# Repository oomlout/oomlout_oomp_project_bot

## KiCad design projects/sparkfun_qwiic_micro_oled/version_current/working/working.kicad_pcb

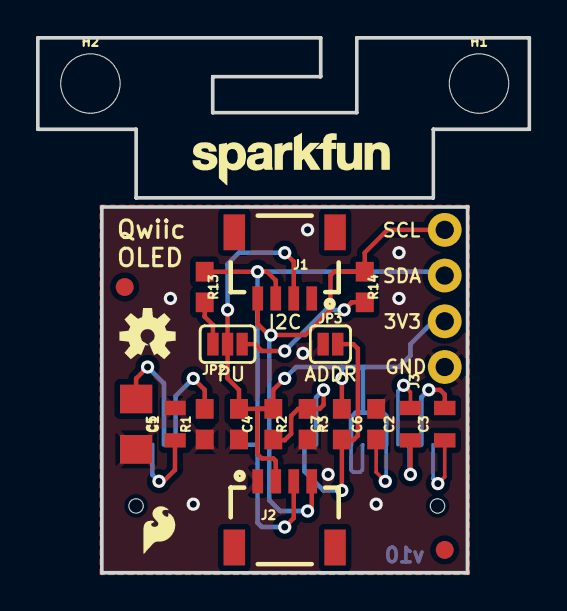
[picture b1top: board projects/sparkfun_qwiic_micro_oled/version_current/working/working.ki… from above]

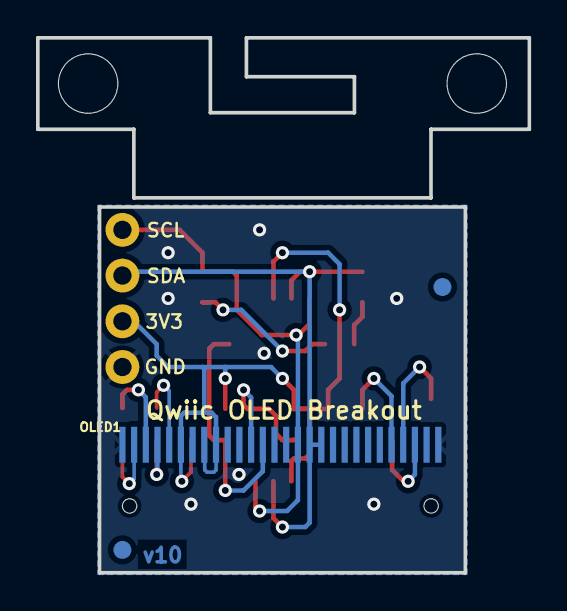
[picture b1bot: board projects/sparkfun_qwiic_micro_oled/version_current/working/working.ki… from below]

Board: 2 copper layers, 27.3 x 29.7 mm, 29 parts (3 on the bottom side), 15 nets.

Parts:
C1: 2.2uF; 0805
C2, C3: 1.0uF; 0805
C4, C6, C7: 1.0uF; 0603
C5: 4.7uF; 1206
FID1, FID2, FID3, FID4: FIDUCIAL1X2; FIDUCIAL-1X2
FRAME1: FRAME-LETTER; CREATIVE_COMMONS
H1, H2: STAND-OFF
J1, J2: 1X04_1MM_RA
J3: 1X04_NO_SILK
JP2: SMT-JUMPER_3_2-NC_PASTE_SILK
JP3: SMT-JUMPER_2_NO_SILK
LOGO1: REVISION
LOGO2: SFE_LOGO_FLAME.1_INCH; SFE_LOGO_FLAME_.1
LOGO3: OSHW-LOGOS; OSHW-LOGO-S
LOGO4: SFE_LOGO_NAME.1_INCH; SFE_LOGO_NAME_.1
OLED1: OLED0.66; OLED-0.66-64X48
R1: 390k; 0603
R2, R3: 10k; 0603
R13, R14: 4.7k; 0603

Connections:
C1P: C2.1, OLED1.4
C2N: C3.2, OLED1.3
D0/SCK: J1.4, J2.4, J3.4, OLED1.16, R14.1
D1/MOSI: J1.3, J2.3, J3.3, OLED1.17, OLED1.18, R13.1
D/C: JP3.2, OLED1.13, R3.1
GND: C1.2, C4.2, C5.2, C6.2, C7.2, J1.1, J2.1, J3.1, JP3.1, OLED1.1, OLED1.7, OLED1.10, OLED1.27, OLED1.28, R1.1
IREF: OLED1.24, R1.2
unnamed: C3.1, OLED1.2
unnamed: C2.2, OLED1.5
unnamed: JP2.3, R13.2
unnamed: JP2.1, R14.2
RESET: C7.1, OLED1.12, R2.2
VCC: C1.1, OLED1.26
VCOMH: C5.1, OLED1.25
VDD: C4.1, C6.1, J1.2, J2.2, J3.2, JP2.2, OLED1.6, OLED1.8, OLED1.9, R2.1, R3.2

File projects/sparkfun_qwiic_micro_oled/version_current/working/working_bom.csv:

"Id";"Designator";"Footprint";"Quantity";"Designation";"Supplier and ref";
1;"C1";"0805";1;"2.2uF";;;
2;"JP3";"SMT-JUMPER_2_NO_SILK";1;"";;;
3;"C6,C7,C4";"0603";3;"1.0uF";;;
4;"R2,R3";"0603";2;"10k";;;
5;"LOGO1";"REVISION";1;"REVISION";;;
6;"R1";"0603";1;"390k";;;
7;"J2,J1";"1X04_1MM_RA";2;"";;;
8;"H1,H2";"STAND-OFF";2;"STAND-OFF";;;
9;"FRAME1";"CREATIVE_COMMONS";1;"FRAME-LETTER";;;
10;"C3,C2";"0805";2;"1.0uF";;;
11;"C5";"1206";1;"4.7uF";;;
12;"LOGO4";"SFE_LOGO_NAME_.1";1;"SFE_LOGO_NAME.1_INCH";;;
13;"JP2";"SMT-JUMPER_3_2-NC_PASTE_SILK";1;"";;;
14;"J3";"1X04_NO_SILK";1;"";;;
15;"LOGO2";"SFE_LOGO_FLAME_.1";1;"SFE_LOGO_FLAME.1_INCH";;;
16;"FID2,FID1,FID4,FID3";"FIDUCIAL-1X2";4;"FIDUCIAL1X2";;;
17;"R14,R13";"0603";2;"4.7k";;;
18;"LOGO3";"OSHW-LOGO-S";1;"OSHW-LOGOS";;;
19;"OLED1";"OLED-0.66-64X48";1;"OLED0.66";;;

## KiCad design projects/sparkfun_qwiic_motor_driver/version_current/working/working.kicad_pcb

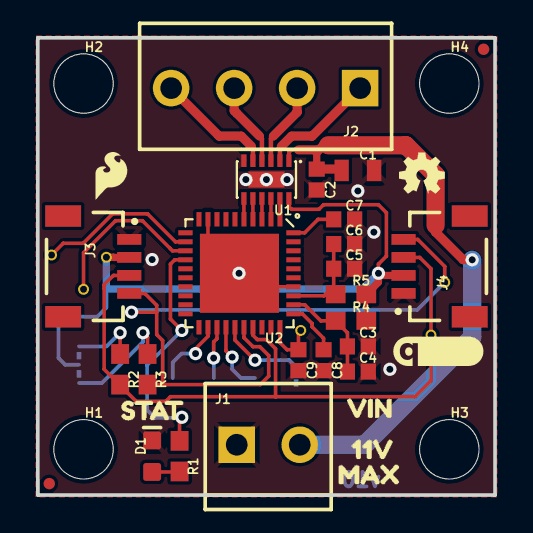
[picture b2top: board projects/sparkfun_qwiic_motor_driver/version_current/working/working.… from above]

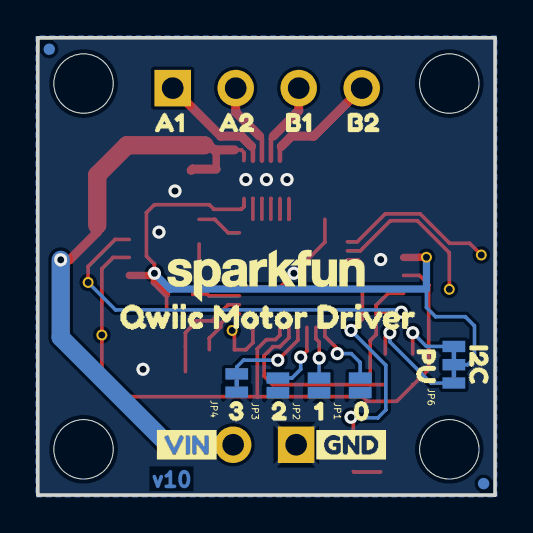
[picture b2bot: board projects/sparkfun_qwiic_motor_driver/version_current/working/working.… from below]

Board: 2 copper layers, 25.4 x 25.4 mm, 62 parts (21 on the bottom side), 29 nets.

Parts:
C1: 10uF; 0805
C2, C4, C6, C9: 0.1uF; 0402
C3, C5, C7, C8: 1.0uF; 0402
D1: BLUE; LED-0603
FD1, FD2, FD3, FD4: FIDUCIALUFIDUCIAL; FIDUCIAL-MICRO
FRAME1: FRAME-LETTER; CREATIVE_COMMONS
H1, H2, H3, H4: STAND-OFF
J1: Power In; SCREWTERMINAL-3.5MM-2
J2: Motor Connections; SCREWTERMINAL-3.5MM-4
J3, J4: Qwiic; JST04_1MM_RA
JP1, JP2, JP3: JUMPER-PAD-2; SMT-JUMPER_2_NO_NO-SILK
JP4: JUMPER-PAD-2; SMT-JUMPER_2_NC_TRACE_NO-SILK
JP6: JUMPER-SMT_3_2-NC_TRACE_NO-SILK; SMT-JUMPER_3_2-NC_TRACE_NO-SILK
LOGO2: OSHW-LOGOMINI; OSHW-LOGO-MINI
LOGO3: SFE_LOGO_NAME.1_INCH; SFE_LOGO_NAME_.1
R1: 470; 0603
R2, R3: 4.7k; 0603
R4, R5: 1; 0603
TP1, TP2, TP3, TP4, TP5, TP6: TP_15TH
U1: DRV8835; WSON-12
U2: CY8C4245LQI-483; QFN-40
U$1: QWIIC_LOGO_5MM; QWIIC_5MM
U$2: STAT4
U$3: GND3
U$4: VIN2
U$5: 05
U$6: 16
U$7: 27
U$8: 38
U$9: A110
U$10: A211
U$11: B112
U$12: B213
U$13: 11V7
U$14: MAX8
U$15: VIN6
U$16: I2C0
U$17: PU1
U$18: QWIIC_MOTOR_DRIVER0
U$19: SFE_LOGO_FLAME_.1

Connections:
3.3V: J3.2, J4.2, JP6.2, R4.2, R5.2, TP1.P$1, U1.12
AOUT1: J2.1, U1.2
AOUT2: J2.2, U1.3
BOUT1: J2.3, U1.4
BOUT2: J2.4, U1.5
GND: C1.2, C2.2, C3.2, C4.2, C5.2, C6.2, C7.2, C8.2, C9.2, D1.C, J1.1, J3.1, J4.1, JP1.1, JP2.1, JP3.1, JP4.1, U1.6, U1.PAD, U2.9, U2.34, U2.EP
MODEB0: JP1.2, U2.22
MODEB1: JP2.2, U2.23
MODEB2: JP3.2, U2.24
MODEB3: JP4.2, U2.25
unnamed: C8.1, U2.31
unnamed: C5.1, C6.1, R5.1, U2.33
unnamed: C7.1, U2.40
unnamed: D1.A, R1.2
unnamed: JP6.1, R3.1
unnamed: JP6.3, R2.1
P2.0: U1.11, U2.1
P2.1: U1.10, U2.2
P2.2: U1.9, U2.3
P2.3: U1.8, U2.4
P2.4: U1.7, U2.5
P3.2: TP2.P$1, U2.12
P3.3: TP3.P$1, U2.13
SCL: J3.4, J4.4, R3.2, TP6.P$1, U2.26
SDA: J3.3, J4.3, R2.2, TP5.P$1, U2.27
SLED: R1.1, U2.14
VDDD: C3.1, C4.1, R4.1, U2.32
VIN: C1.1, C2.1, J1.2, U1.1
~RESET: C9.1, TP4.P$1, U2.30

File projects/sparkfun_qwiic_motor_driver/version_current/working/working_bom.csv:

"Id";"Designator";"Footprint";"Quantity";"Designation";"Supplier and ref";
1;"H4,H3,H1,H2";"STAND-OFF";4;"STAND-OFF";;;
2;"TP5,TP2,TP3,TP4,TP1,TP6";"TP_15TH";6;"";;;
3;"C5,C7,C3,C8";"0402";4;"1.0uF";;;
4;"C9,C6,C2,C4";"0402";4;"0.1uF";;;
5;"U$1";"QWIIC_5MM";1;"QWIIC_LOGO_5MM";;;
6;"FD1,FD3,FD2,FD4";"FIDUCIAL-MICRO";4;"FIDUCIALUFIDUCIAL";;;
7;"U1";"WSON-12";1;"DRV8835";;;
8;"C1";"0805";1;"10uF";;;
9;"J4,J3";"JST04_1MM_RA";2;"Qwiic";;;
10;"U2";"QFN-40";1;"CY8C4245LQI-483";;;
11;"FRAME1";"CREATIVE_COMMONS";1;"FRAME-LETTER";;;
12;"U$14";"MAX8";1;"";;;
13;"R2,R3";"0603";2;"4.7k";;;
14;"U$13";"11V7";1;"";;;
15;"LOGO2";"OSHW-LOGO-MINI";1;"OSHW-LOGOMINI";;;
16;"R1";"0603";1;"470";;;
17;"J2";"SCREWTERMINAL-3.5MM-4";1;"Motor Connections";;;
18;"R4,R5";"0603";2;"1";;;
19;"U$15";"VIN6";1;"";;;
20;"U$2";"STAT4";1;"";;;
21;"U$19";"SFE_LOGO_FLAME_.1";1;"";;;
22;"D1";"LED-0603";1;"BLUE";;;
23;"J1";"SCREWTERMINAL-3.5MM-2";1;"Power In";;;
24;"U$16";"I2C0";1;"";;;
25;"JP3,JP1,JP2";"SMT-JUMPER_2_NO_NO-SILK";3;"JUMPER-PAD-2";;;
26;"JP4";"SMT-JUMPER_2_NC_TRACE_NO-SILK";1;"JUMPER-PAD-2";;;
27;"LOGO3";"SFE_LOGO_NAME_.1";1;"SFE_LOGO_NAME.1_INCH";;;
28;"U$8";"38";1;"";;;
29;"U$11";"B112";1;"";;;
30;"U$18";"QWIIC_MOTOR_DRIVER0";1;"";;;
31;"U$4";"VIN2";1;"";;;
32;"U$7";"27";1;"";;;
33;"U$5";"05";1;"";;;
34;"U$10";"A211";1;"";;;
35;"U$17";"PU1";1;"";;;
36;"U$6";"16";1;"";;;
37;"U$12";"B213";1;"";;;
38;"U$9";"A110";1;"";;;
39;"JP6";"SMT-JUMPER_3_2-NC_TRACE_NO-SILK";1;"JUMPER-SMT_3_2-NC_TRACE_NO-SILK";;;
40;"U$3";"GND3";1;"";;;

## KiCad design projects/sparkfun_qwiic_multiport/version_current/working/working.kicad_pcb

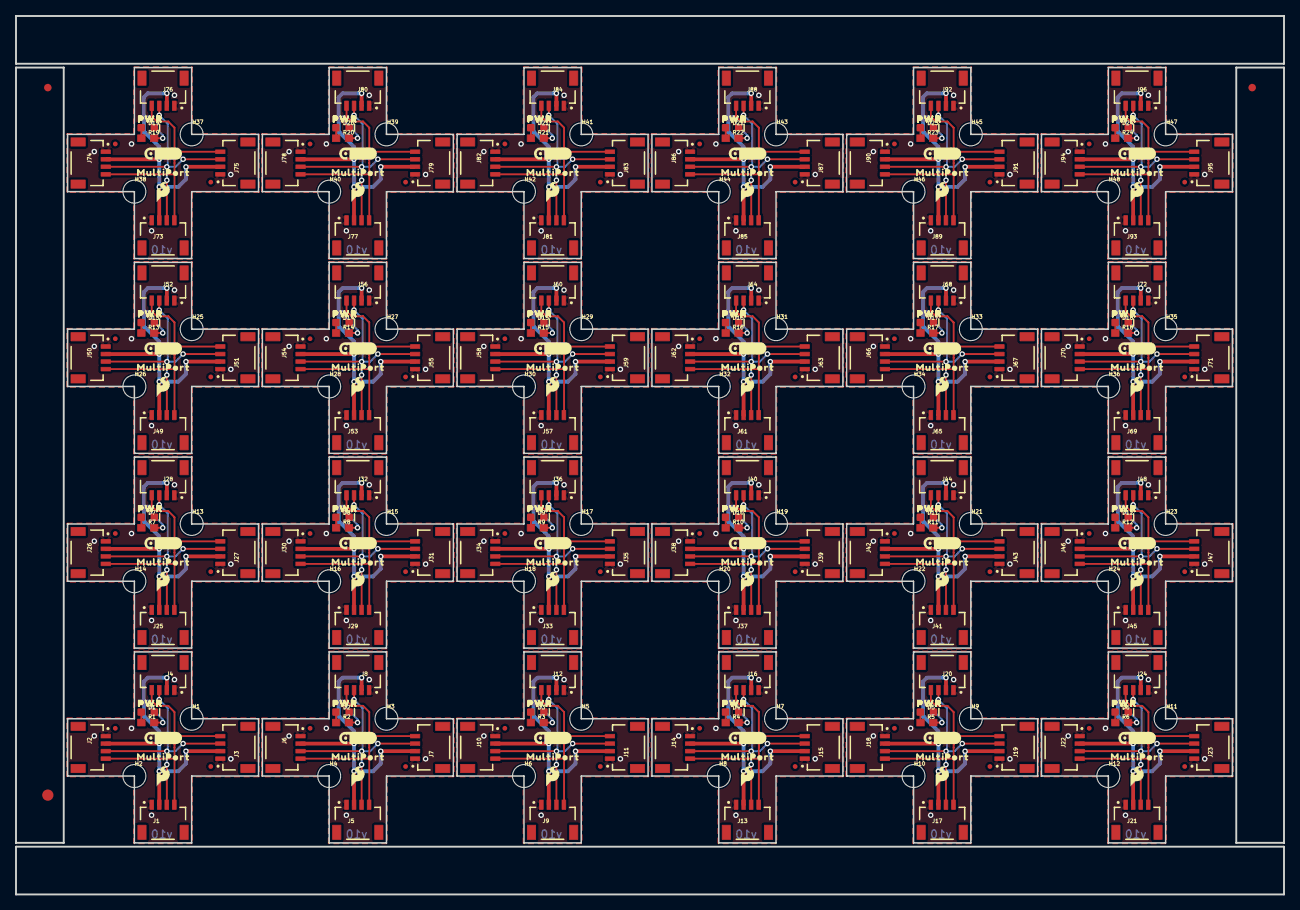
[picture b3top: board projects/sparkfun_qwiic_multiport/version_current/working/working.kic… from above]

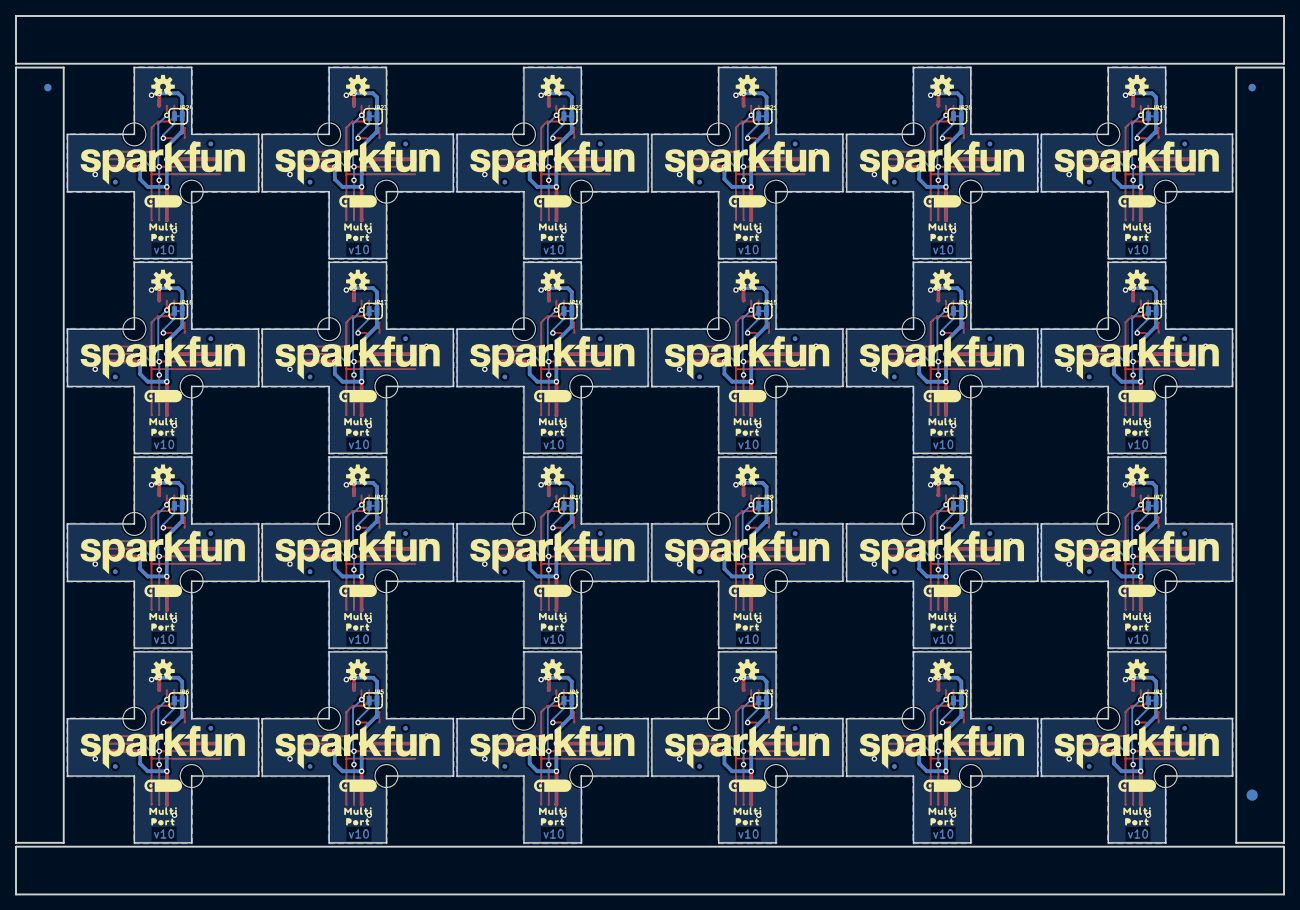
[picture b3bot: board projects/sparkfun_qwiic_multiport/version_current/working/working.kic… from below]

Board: 2 copper layers, 168.7 x 116.8 mm, 582 parts (219 on the bottom side), 144 nets.

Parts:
D1, D2, D3, D4, D5, D6, D7, D8, D9, D10, D11, D12, D13, D14, D15, D16, D17, D18, D19, D20, D21, D22, D23, D24: RED; LED-0603
E$1, E$2, E$3, E$4: FIDUCIAL-1X2
E$5, E$6: FIDUCIAL-1.5X3
FD1, FD2, FD3, FD4, FD5, FD6, FD7, FD8, FD9, FD10, FD11, FD12, FD13, FD14, FD15, FD16, FD17, FD18, FD19, FD20, FD21, FD22, FD23, FD24, FD25, FD26, FD27, FD28, FD29, FD30, FD31, FD32, FD33, FD34, FD35, FD36, FD37, FD38, FD39, FD40, FD41, FD42, FD43, FD44, FD45, FD46, FD47, FD48, FD49, FD50, FD51, FD52, FD53, FD54, FD55, FD56, FD57, FD58, FD59, FD60, FD61, FD62, FD63, FD64, FD65, FD66, FD67, FD68, FD69, FD70, FD71, FD72, FD73, FD74, FD75, FD76, FD77, FD78, FD79, FD80, FD81, FD82, FD83, FD84, FD85, FD86, FD87, FD88, FD89, FD90, FD91, FD92, FD93, FD94, FD95, FD96: FIDUCIALUFIDUCIAL; FIDUCIAL-MICRO
H1, H2, H3, H4, H5, H6, H7, H8, H9, H10, H11, H12, H13, H14, H15, H16, H17, H18, H19, H20, H21, H22, H23, H24, H25, H26, H27, H28, H29, H30, H31, H32, H33, H34, H35, H36, H37, H38, H39, H40, H41, H42, H43, H44, H45, H46, H47, H48: STAND-OFFTIGHT; STAND-OFF-TIGHT
J1, J2, J3, J4, J5, J6, J7, J8, J9, J10, J11, J12, J13, J14, J15, J16, J17, J18, J19, J20, J21, J22, J23, J24, J25, J26, J27, J28, J29, J30, J31, J32, J33, J34, J35, J36, J37, J38, J39, J40, J41, J42, J43, J44, J45, J46, J47, J48, J49, J50, J51, J52, J53, J54, J55, J56, J57, J58, J59, J60, J61, J62, J63, J64, J65, J66, J67, J68, J69, J70, J71, J72, J73, J74, J75, J76, J77, J78, J79, J80, J81, J82, J83, J84, J85, J86, J87, J88, J89, J90, J91, J92, J93, J94, J95, J96: QWIIC_RIGHT_ANGLE; JST04_1MM_RA
JP1, JP2, JP3, JP4, JP5, JP6, JP7, JP8, JP9, JP10, JP11, JP12, JP13, JP14, JP15, JP16, JP17, JP18, JP19, JP20, JP21, JP22, JP23, JP24: PWR_LED; SMT-JUMPER_2_NC_TRACE_SILK
LOGO1, LOGO2, LOGO5, LOGO6, LOGO9, LOGO10, LOGO13, LOGO14, LOGO17, LOGO18, LOGO21, LOGO22, LOGO25, LOGO26, LOGO29, LOGO30, LOGO33, LOGO34, LOGO37, LOGO38, LOGO41, LOGO42, LOGO45, LOGO46, LOGO49, LOGO50, LOGO53, LOGO54, LOGO57, LOGO58, LOGO61, LOGO62, LOGO65, LOGO66, LOGO69, LOGO70, LOGO73, LOGO74, LOGO77, LOGO78, LOGO81, LOGO82, LOGO85, LOGO86, LOGO89, LOGO90, LOGO93, LOGO94: QWIIC_LOGO_5MM; QWIIC_5MM
LOGO3, LOGO7, LOGO11, LOGO15, LOGO19, LOGO23, LOGO27, LOGO31, LOGO35, LOGO39, LOGO43, LOGO47, LOGO51, LOGO55, LOGO59, LOGO63, LOGO67, LOGO71, LOGO75, LOGO79, LOGO83, LOGO87, LOGO91, LOGO95: OSHW-LOGOS; OSHW-LOGO-S
LOGO4, LOGO8, LOGO12, LOGO16, LOGO20, LOGO24, LOGO28, LOGO32, LOGO36, LOGO40, LOGO44, LOGO48, LOGO52, LOGO56, LOGO60, LOGO64, LOGO68, LOGO72, LOGO76, LOGO80, LOGO84, LOGO88, LOGO92, LOGO96: SFE_LOGO_NAME.2_INCH; SFE_LOGO_NAME_.2
R1, R2, R3, R4, R5, R6, R7, R8, R9, R10, R11, R12, R13, R14, R15, R16, R17, R18, R19, R20, R21, R22, R23, R24: 1k; 0603
U$1, U$6, U$9, U$10, U$16, U$19, U$23, U$26, U$30, U$33, U$37, U$40, U$44, U$47, U$51, U$54, U$58, U$61, U$65, U$68, U$72, U$75, U$79, U$82, U$86, U$89, U$93, U$96, U$100, U$103, U$107, U$110, U$114, U$117, U$121, U$124, U$128, U$131, U$135, U$138, U$142, U$145, U$149, U$152, U$156, U$159, U$163, U$166: PWR0
U$2, U$3, U$15, U$22, U$29, U$36, U$43, U$50, U$57, U$64, U$71, U$78, U$85, U$92, U$99, U$106, U$113, U$120, U$127, U$134, U$141, U$148, U$155, U$162: SFE_LOGO_FLAME_.1
U$4, U$12, U$20, U$27, U$34, U$41, U$48, U$55, U$62, U$69, U$76, U$83, U$90, U$97, U$104, U$111, U$118, U$125, U$132, U$139, U$146, U$153, U$160, U$167: MULTIPORT0
U$5, U$14, U$21, U$28, U$35, U$42, U$49, U$56, U$63, U$70, U$77, U$84, U$91, U$98, U$105, U$112, U$119, U$126, U$133, U$140, U$147, U$154, U$161, U$168: #PWR#0
U$7, U$11, U$17, U$24, U$31, U$38, U$45, U$52, U$59, U$66, U$73, U$80, U$87, U$94, U$101, U$108, U$115, U$122, U$129, U$136, U$143, U$150, U$157, U$164: MULTI0
U$8, U$13, U$18, U$25, U$32, U$39, U$46, U$53, U$60, U$67, U$74, U$81, U$88, U$95, U$102, U$109, U$116, U$123, U$130, U$137, U$144, U$151, U$158, U$165: PORT0

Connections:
3.3V: J1.2, J2.2, J3.2, J4.2, JP1.2
3.3V1: J5.2, J6.2, J7.2, J8.2, JP2.2
3.3V2: J9.2, J10.2, J11.2, J12.2, JP3.2
3.3V3: J13.2, J14.2, J15.2, J16.2, JP4.2
3.3V4: J17.2, J18.2, J19.2, J20.2, JP5.2
3.3V5: J21.2, J22.2, J23.2, J24.2, JP6.2
3.3V6: J25.2, J26.2, J27.2, J28.2, JP7.2
3.3V7: J29.2, J30.2, J31.2, J32.2, JP8.2
3.3V8: J33.2, J34.2, J35.2, J36.2, JP9.2
3.3V9: J37.2, J38.2, J39.2, J40.2, JP10.2
3.3V10: J41.2, J42.2, J43.2, J44.2, JP11.2
3.3V11: J45.2, J46.2, J47.2, J48.2, JP12.2
3.3V12: J49.2, J50.2, J51.2, J52.2, JP13.2
3.3V13: J53.2, J54.2, J55.2, J56.2, JP14.2
3.3V14: J57.2, J58.2, J59.2, J60.2, JP15.2
3.3V15: J61.2, J62.2, J63.2, J64.2, JP16.2
3.3V16: J65.2, J66.2, J67.2, J68.2, JP17.2
3.3V17: J69.2, J70.2, J71.2, J72.2, JP18.2
3.3V18: J73.2, J74.2, J75.2, J76.2, JP19.2
3.3V19: J77.2, J78.2, J79.2, J80.2, JP20.2
3.3V20: J81.2, J82.2, J83.2, J84.2, JP21.2
3.3V21: J85.2, J86.2, J87.2, J88.2, JP22.2
3.3V22: J89.2, J90.2, J91.2, J92.2, JP23.2
3.3V23: J93.2, J94.2, J95.2, J96.2, JP24.2
GND: D1.C, J1.1, J2.1, J3.1, J4.1
GND1: D2.C, J5.1, J6.1, J7.1, J8.1
GND2: D3.C, J9.1, J10.1, J11.1, J12.1
GND3: D4.C, J13.1, J14.1, J15.1, J16.1
GND4: D5.C, J17.1, J18.1, J19.1, J20.1
GND5: D6.C, J21.1, J22.1, J23.1, J24.1
GND6: D7.C, J25.1, J26.1, J27.1, J28.1
GND7: D8.C, J29.1, J30.1, J31.1, J32.1
GND8: D9.C, J33.1, J34.1, J35.1, J36.1
GND9: D10.C, J37.1, J38.1, J39.1, J40.1
GND10: D11.C, J41.1, J42.1, J43.1, J44.1
GND11: D12.C, J45.1, J46.1, J47.1, J48.1
GND12: D13.C, J49.1, J50.1, J51.1, J52.1
GND13: D14.C, J53.1, J54.1, J55.1, J56.1
GND14: D15.C, J57.1, J58.1, J59.1, J60.1
GND15: D16.C, J61.1, J62.1, J63.1, J64.1
GND16: D17.C, J65.1, J66.1, J67.1, J68.1
GND17: D18.C, J69.1, J70.1, J71.1, J72.1
GND18: D19.C, J73.1, J74.1, J75.1, J76.1
GND19: D20.C, J77.1, J78.1, J79.1, J80.1
GND20: D21.C, J81.1, J82.1, J83.1, J84.1
GND21: D22.C, J85.1, J86.1, J87.1, J88.1
GND22: D23.C, J89.1, J90.1, J91.1, J92.1
GND23: D24.C, J93.1, J94.1, J95.1, J96.1
unnamed: D1.A, R1.1
unnamed: JP1.1, R1.2
unnamed: D2.A, R2.1
unnamed: JP2.1, R2.2
unnamed: D3.A, R3.1
unnamed: JP3.1, R3.2
unnamed: D4.A, R4.1
unnamed: JP4.1, R4.2
unnamed: D5.A, R5.1
unnamed: JP5.1, R5.2
unnamed: D6.A, R6.1
unnamed: JP6.1, R6.2
unnamed: D7.A, R7.1
unnamed: JP7.1, R7.2
unnamed: D8.A, R8.1
unnamed: JP8.1, R8.2
unnamed: D9.A, R9.1
unnamed: JP9.1, R9.2
unnamed: D10.A, R10.1
unnamed: JP10.1, R10.2
unnamed: D11.A, R11.1
unnamed: JP11.1, R11.2
unnamed: D12.A, R12.1
unnamed: JP12.1, R12.2
unnamed: D13.A, R13.1
unnamed: JP13.1, R13.2
unnamed: D14.A, R14.1
unnamed: JP14.1, R14.2
unnamed: D15.A, R15.1
unnamed: JP15.1, R15.2
unnamed: D16.A, R16.1
unnamed: JP16.1, R16.2
unnamed: D17.A, R17.1
unnamed: JP17.1, R17.2
unnamed: D18.A, R18.1
unnamed: JP18.1, R18.2
unnamed: D19.A, R19.1
unnamed: JP19.1, R19.2
unnamed: D20.A, R20.1
unnamed: JP20.1, R20.2
unnamed: D21.A, R21.1
unnamed: JP21.1, R21.2
unnamed: D22.A, R22.1
unnamed: JP22.1, R22.2
unnamed: D23.A, R23.1
unnamed: JP23.1, R23.2
unnamed: D24.A, R24.1
unnamed: JP24.1, R24.2
SCL: J1.4, J2.4, J3.4, J4.4
SCL1: J5.4, J6.4, J7.4, J8.4
SCL2: J9.4, J10.4, J11.4, J12.4
SCL3: J13.4, J14.4, J15.4, J16.4
SCL4: J17.4, J18.4, J19.4, J20.4
SCL5: J21.4, J22.4, J23.4, J24.4
SCL6: J25.4, J26.4, J27.4, J28.4
SCL7: J29.4, J30.4, J31.4, J32.4
SCL8: J33.4, J34.4, J35.4, J36.4
SCL9: J37.4, J38.4, J39.4, J40.4
SCL10: J41.4, J42.4, J43.4, J44.4
SCL11: J45.4, J46.4, J47.4, J48.4
SCL12: J49.4, J50.4, J51.4, J52.4
SCL13: J53.4, J54.4, J55.4, J56.4
SCL14: J57.4, J58.4, J59.4, J60.4
SCL15: J61.4, J62.4, J63.4, J64.4
SCL16: J65.4, J66.4, J67.4, J68.4
SCL17: J69.4, J70.4, J71.4, J72.4
SCL18: J73.4, J74.4, J75.4, J76.4
SCL19: J77.4, J78.4, J79.4, J80.4
SCL20: J81.4, J82.4, J83.4, J84.4
SCL21: J85.4, J86.4, J87.4, J88.4
SCL22: J89.4, J90.4, J91.4, J92.4
SCL23: J93.4, J94.4, J95.4, J96.4
SDA: J1.3, J2.3, J3.3, J4.3
SDA1: J5.3, J6.3, J7.3, J8.3
SDA2: J9.3, J10.3, J11.3, J12.3
SDA3: J13.3, J14.3, J15.3, J16.3
SDA4: J17.3, J18.3, J19.3, J20.3
SDA5: J21.3, J22.3, J23.3, J24.3
SDA6: J25.3, J26.3, J27.3, J28.3
SDA7: J29.3, J30.3, J31.3, J32.3
SDA8: J33.3, J34.3, J35.3, J36.3
SDA9: J37.3, J38.3, J39.3, J40.3
SDA10: J41.3, J42.3, J43.3, J44.3
SDA11: J45.3, J46.3, J47.3, J48.3
SDA12: J49.3, J50.3, J51.3, J52.3
SDA13: J53.3, J54.3, J55.3, J56.3
SDA14: J57.3, J58.3, J59.3, J60.3
SDA15: J61.3, J62.3, J63.3, J64.3
SDA16: J65.3, J66.3, J67.3, J68.3
SDA17: J69.3, J70.3, J71.3, J72.3
SDA18: J73.3, J74.3, J75.3, J76.3
SDA19: J77.3, J78.3, J79.3, J80.3
SDA20: J81.3, J82.3, J83.3, J84.3
SDA21: J85.3, J86.3, J87.3, J88.3
SDA22: J89.3, J90.3, J91.3, J92.3
SDA23: J93.3, J94.3, J95.3, J96.3

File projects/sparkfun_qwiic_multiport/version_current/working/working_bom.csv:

"Id";"Designator";"Footprint";"Quantity";"Designation";"Supplier and ref";
1;"J83,J76,J38,J96,J58,J16,J54,J42,J95,J13,J37,J47,J34,J22,J89,J63,J60,J69,J92,J73,J90,J6,J53,J57,J7,J39,J75,J1,J45,J55,J82,J59,J10,J51,J20,J61,J56,J86,J77,J30,J72,J64,J12,J67,J91,J4,J74,J46,J15,J44,J27,J35,J14,J48,J81,J19,J26,J5,J21,J62,J23,J50,J43,J87,J52,J25,J8,J70,J88,J17,J28,J18,J68,J32,J66,J29,J11,J41,J85,J84,J80,J93,J2,J36,J33,J71,J49,J24,J3,J94,J79,J9,J31,J78,J65,J40";"JST04_1MM_RA";96;"QWIIC_RIGHT_ANGLE";;;
2;"R6,R4,R18,R13,R11,R20,R12,R22,R16,R1,R5,R24,R9,R3,R17,R21,R2,R19,R14,R23,R7,R15,R8,R10";"0603";24;"1k";;;
3;"LOGO89,LOGO5,LOGO41,LOGO53,LOGO29,LOGO57,LOGO85,LOGO33,LOGO17,LOGO13,LOGO93,LOGO77,LOGO37,LOGO9,LOGO25,LOGO65,LOGO81,LOGO73,LOGO21,LOGO61,LOGO69,LOGO49,LOGO1,LOGO45,LOGO62,LOGO46,LOGO58,LOGO82,LOGO74,LOGO38,LOGO78,LOGO26,LOGO30,LOGO50,LOGO90,LOGO66,LOGO94,LOGO14,LOGO6,LOGO34,LOGO70,LOGO42,LOGO54,LOGO22,LOGO18,LOGO10,LOGO86,LOGO2";"QWIIC_5MM";48;"QWIIC_LOGO_5MM";;;
4;"FD46,FD15,FD18,FD87,FD54,FD39,FD19,FD2,FD55,FD43,FD50,FD86,FD31,FD79,FD51,FD11,FD22,FD78,FD66,FD38,FD7,FD26,FD27,FD62,FD59,FD14,FD6,FD30,FD75,FD91,FD23,FD42,FD71,FD58,FD83,FD94,FD34,FD90,FD67,FD82,FD3,FD47,FD74,FD70,FD10,FD63,FD95,FD35,FD37,FD17,FD21,FD32,FD89,FD72,FD96,FD29,FD73,FD52,FD81,FD44,FD1,FD64,FD60,FD77,FD13,FD24,FD40,FD33,FD16,FD68,FD80,FD65,FD48,FD5,FD76,FD25,FD45,FD9,FD92,FD69,FD88,FD20,FD56,FD53,FD57,FD4,FD49,FD12,FD8,FD41,FD36,FD28,FD85,FD61,FD93,FD84";"FIDUCIAL-MICRO";96;"FIDUCIALUFIDUCIAL";;;
5;"D12,D14,D8,D24,D9,D1,D18,D17,D19,D13,D10,D15,D16,D11,D22,D4,D2,D21,D5,D3,D20,D6,D23,D7";"LED-0603";24;"RED";;;
6;"H33,H21,H12,H48,H15,H25,H45,H30,H5,H38,H23,H11,H42,H14,H29,H28,H8,H18,H1,H22,H47,H37,H39,H17,H4,H34,H13,H36,H20,H19,H26,H7,H40,H24,H16,H46,H35,H43,H32,H41,H44,H2,H9,H6,H27,H3,H31,H10";"STAND-OFF-TIGHT";48;"STAND-OFFTIGHT";;;
7;"U$152,U$149,U$100,U$86,U$96,U$107,U$124,U$9,U$68,U$79,U$44,U$117,U$156,U$30,U$16,U$47,U$72,U$6,U$10,U$103,U$110,U$82,U$135,U$33,U$61,U$23,U$1,U$128,U$145,U$54,U$51,U$142,U$163,U$26,U$131,U$89,U$121,U$75,U$37,U$58,U$114,U$40,U$138,U$93,U$65,U$166,U$19,U$159";"PWR0";48;"";;;
8;"U$90,U$125,U$132,U$69,U$153,U$76,U$104,U$160,U$97,U$118,U$55,U$41,U$167,U$12,U$48,U$34,U$20,U$27,U$146,U$83,U$4,U$139,U$62,U$111";"MULTIPORT0";24;"";;;
9;"E$1,E$3,E$4,E$2";"FIDUCIAL-1X2";4;"";;;
10;"U$2,U$99,U$148,U$141,U$127,U$43,U$85,U$71,U$92,U$134,U$36,U$64,U$15,U$113,U$57,U$3,U$106,U$162,U$155,U$120,U$78,U$50,U$29,U$22";"SFE_LOGO_FLAME_.1";24;"";;;
11;"E$5,E$6";"FIDUCIAL-1.5X3";2;"";;;
12;"LOGO8,LOGO92,LOGO64,LOGO4,LOGO44,LOGO88,LOGO48,LOGO56,LOGO68,LOGO76,LOGO36,LOGO20,LOGO96,LOGO40,LOGO84,LOGO72,LOGO12,LOGO52,LOGO60,LOGO16,LOGO80,LOGO28,LOGO24,LOGO32";"SFE_LOGO_NAME_.2";24;"SFE_LOGO_NAME.2_INCH";;;
13;"U$63,U$35,U$70,U$91,U$105,U$5,U$133,U$77,U$161,U$112,U$140,U$21,U$119,U$56,U$14,U$154,U$42,U$84,U$126,U$168,U$49,U$147,U$98,U$28";"#PWR#0";24;"";;;
14;"JP2,JP22,JP3,JP6,JP21,JP16,JP17,JP20,JP9,JP14,JP5,JP11,JP8,JP15,JP23,JP12,JP13,JP4,JP10,JP7,JP1,JP18,JP24,JP19";"SMT-JUMPER_2_NC_TRACE_SILK";24;"PWR_LED";;;
15;"LOGO95,LOGO19,LOGO39,LOGO23,LOGO75,LOGO67,LOGO31,LOGO79,LOGO43,LOGO55,LOGO3,LOGO59,LOGO7,LOGO91,LOGO47,LOGO63,LOGO11,LOGO15,LOGO35,LOGO71,LOGO87,LOGO83,LOGO51,LOGO27";"OSHW-LOGO-S";24;"OSHW-LOGOS";;;
16;"U$46,U$151,U$53,U$81,U$95,U$130,U$144,U$67,U$18,U$60,U$88,U$165,U$13,U$25,U$109,U$137,U$39,U$102,U$116,U$74,U$32,U$158,U$8,U$123";"PORT0";24;"";;;
17;"U$38,U$164,U$150,U$101,U$129,U$11,U$94,U$73,U$157,U$24,U$122,U$45,U$136,U$52,U$87,U$66,U$31,U$115,U$17,U$7,U$59,U$80,U$108,U$143";"MULTI0";24;"";;;

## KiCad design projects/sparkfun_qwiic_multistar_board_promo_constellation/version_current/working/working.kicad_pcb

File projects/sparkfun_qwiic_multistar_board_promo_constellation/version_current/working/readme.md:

# Qwiic_MultiStar_Board_Promo_Constellation by sparkfun  
This is a harvested standardized copy of a project from github.  
The original project can be found at:  
https://github.com/sparkfun/Qwiic_MultiStar_Board_Promo_Constellation  
Please consult that link for additional, details, files, and license information.  
Note: It was auto harvested and if the original repo had more than one board file or anything out of the ordinary the files here are likely not representative.

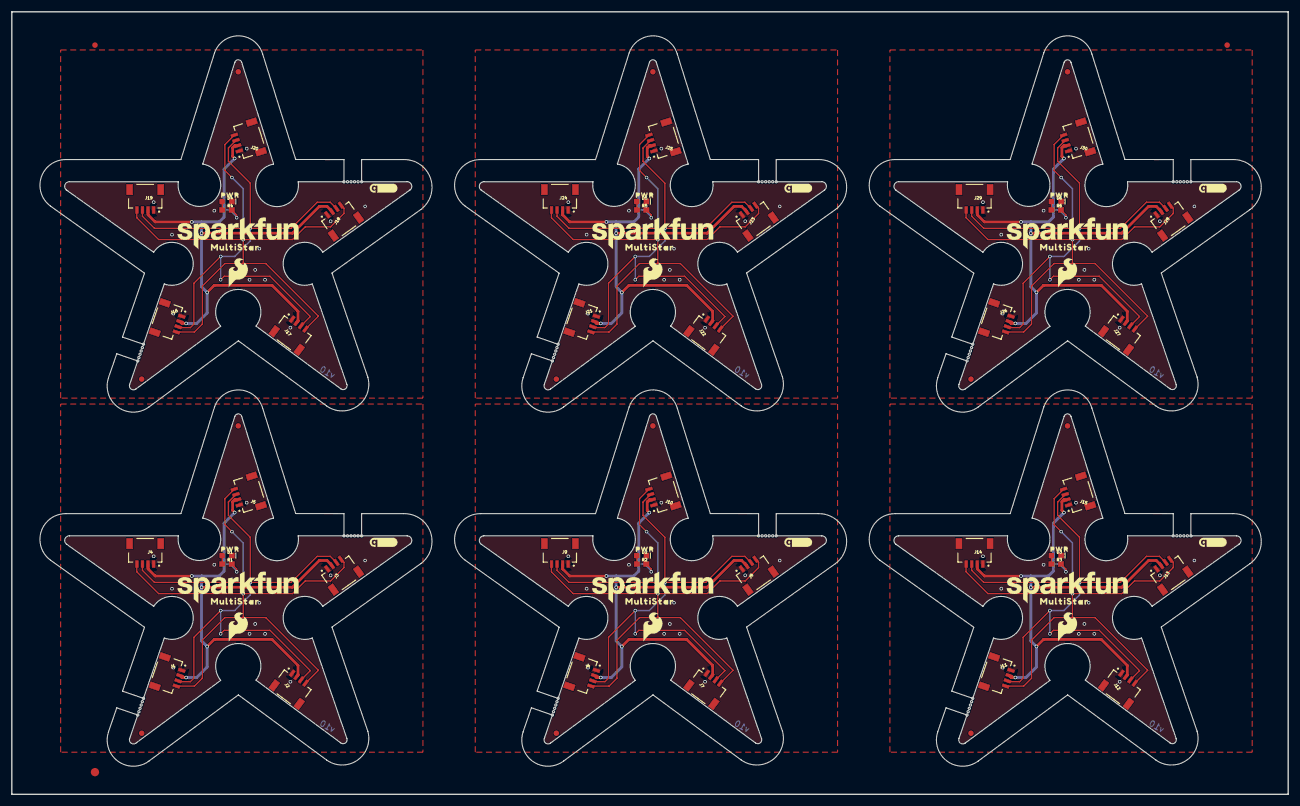
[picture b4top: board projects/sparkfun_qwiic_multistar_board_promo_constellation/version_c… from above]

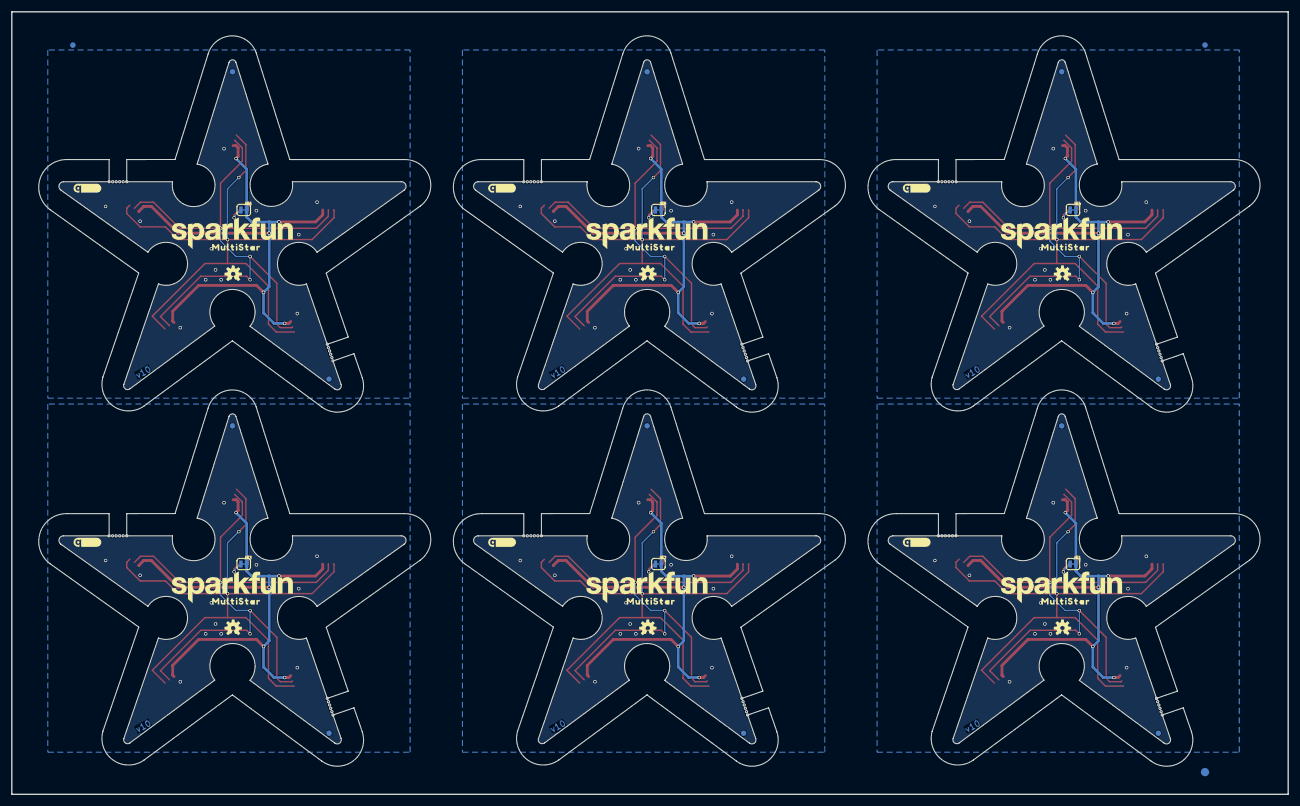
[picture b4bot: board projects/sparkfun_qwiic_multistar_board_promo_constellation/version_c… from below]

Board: 2 copper layers, 230.0 x 141.0 mm, 210 parts (51 on the bottom side), 36 nets.

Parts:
@HOLE0, @HOLE1, @HOLE2, @HOLE3, @HOLE4, @HOLE5, @HOLE6, @HOLE7, @HOLE8, @HOLE9, @HOLE10, @HOLE11, @HOLE12, @HOLE13, @HOLE14, @HOLE15, @HOLE16, @HOLE17, @HOLE18, @HOLE19, @HOLE20, @HOLE21, @HOLE22, @HOLE23, @HOLE24, @HOLE25, @HOLE26, @HOLE27, @HOLE28, @HOLE29, @HOLE30, @HOLE31, @HOLE32, @HOLE33, @HOLE34, @HOLE35, @HOLE36, @HOLE37, @HOLE38, @HOLE39, @HOLE40, @HOLE41, @HOLE42, @HOLE43, @HOLE44, @HOLE45, @HOLE46, @HOLE47, @HOLE48, @HOLE49, @HOLE50, @HOLE51, @HOLE52, @HOLE53, @HOLE54, @HOLE55, @HOLE56, @HOLE57, @HOLE58, @HOLE59, @HOLE60, @HOLE61, @HOLE62, @HOLE63, @HOLE64, @HOLE65, @HOLE66, @HOLE67, @HOLE68, @HOLE69, @HOLE70, @HOLE71: (no value)
D1, D2, D3, D4, D5, D6: RED; LED-0603
E$1, E$2, E$3, E$4: FIDUCIAL-1X2
E$5, E$6: FIDUCIAL-1.5X3
FD1, FD2, FD3, FD4, FD5, FD6, FD7, FD8, FD9, FD10, FD11, FD12, FD13, FD14, FD15, FD16, FD17, FD18, FD19, FD20, FD21, FD22, FD23, FD24: FIDUCIAL1X2; FIDUCIAL-1X2
J1, J2, J3, J4, J5, J6, J7, J8, J9, J10, J11, J12, J13, J14, J15, J16, J17, J18, J19, J20, J21, J22, J23, J24, J25, J26, J27, J28, J29, J30: QWIIC_RIGHT_ANGLE; JST04_1MM_RA
JP1, JP2, JP3, JP4, JP5, JP6: PWR_LED; SMT-JUMPER_2_NC_TRACE_SILK
LOGO1, LOGO2, LOGO6, LOGO7, LOGO11, LOGO12, LOGO16, LOGO17, LOGO21, LOGO22, LOGO26, LOGO27: QWIIC_LOGO_5MM; QWIIC_5MM
LOGO3, LOGO8, LOGO13, LOGO18, LOGO23, LOGO28: OSHW-LOGOS; OSHW-LOGO-S
LOGO4, LOGO5, LOGO9, LOGO10, LOGO14, LOGO15, LOGO19, LOGO20, LOGO24, LOGO25, LOGO29, LOGO30: SFE_LOGO_NAME.2_INCH; SFE_LOGO_NAME_.2
R1, R2, R3, R4, R5, R6: 1k; 0603
U$1, U$9, U$11, U$16, U$21, U$26: PWR0
U$2, U$4, U$12, U$17, U$22, U$27: SFE_LOGO_FLAME_.2
U$3, U$5, U$7, U$8, U$13, U$14, U$18, U$19, U$23, U$24, U$28, U$29: MULTISTAR0
U$6, U$10, U$15, U$20, U$25, U$30: #PWR#0

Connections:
3.3V: J1.2, J2.2, J3.2, J4.2, J5.2, JP1.2
3.3V1: J6.2, J7.2, J8.2, J9.2, J10.2, JP2.2
3.3V2: J11.2, J12.2, J13.2, J14.2, J15.2, JP3.2
3.3V3: J16.2, J17.2, J18.2, J19.2, J20.2, JP4.2
3.3V4: J21.2, J22.2, J23.2, J24.2, J25.2, JP5.2
3.3V5: J26.2, J27.2, J28.2, J29.2, J30.2, JP6.2
GND: D1.C, J1.1, J2.1, J3.1, J4.1, J5.1
GND1: D2.C, J6.1, J7.1, J8.1, J9.1, J10.1
GND2: D3.C, J11.1, J12.1, J13.1, J14.1, J15.1
GND3: D4.C, J16.1, J17.1, J18.1, J19.1, J20.1
GND4: D5.C, J21.1, J22.1, J23.1, J24.1, J25.1
GND5: D6.C, J26.1, J27.1, J28.1, J29.1, J30.1
unnamed: D1.A, R1.1
unnamed: JP1.1, R1.2
unnamed: D2.A, R2.1
unnamed: JP2.1, R2.2
unnamed: D3.A, R3.1
unnamed: JP3.1, R3.2
unnamed: D4.A, R4.1
unnamed: JP4.1, R4.2
unnamed: D5.A, R5.1
unnamed: JP5.1, R5.2
unnamed: D6.A, R6.1
unnamed: JP6.1, R6.2
SCL: J1.4, J2.4, J3.4, J4.4, J5.4
SCL1: J6.4, J7.4, J8.4, J9.4, J10.4
SCL2: J11.4, J12.4, J13.4, J14.4, J15.4
SCL3: J16.4, J17.4, J18.4, J19.4, J20.4
SCL4: J21.4, J22.4, J23.4, J24.4, J25.4
SCL5: J26.4, J27.4, J28.4, J29.4, J30.4
SDA: J1.3, J2.3, J3.3, J4.3, J5.3
SDA1: J6.3, J7.3, J8.3, J9.3, J10.3
SDA2: J11.3, J12.3, J13.3, J14.3, J15.3
SDA3: J16.3, J17.3, J18.3, J19.3, J20.3
SDA4: J21.3, J22.3, J23.3, J24.3, J25.3
SDA5: J26.3, J27.3, J28.3, J29.3, J30.3

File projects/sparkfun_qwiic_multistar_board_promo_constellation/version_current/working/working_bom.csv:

"Id";"Designator";"Footprint";"Quantity";"Designation";"Supplier and ref";
1;"@HOLE24,@HOLE14,@HOLE38,@HOLE4,@HOLE37,@HOLE41,@HOLE31,@HOLE44,@HOLE33,@HOLE15,@HOLE45,@HOLE40,@HOLE3,@HOLE19,@HOLE11,@HOLE67,@HOLE35,@HOLE12,@HOLE54,@HOLE59,@HOLE51,@HOLE57,@HOLE47,@HOLE25,@HOLE71,@HOLE6,@HOLE23,@HOLE16,@HOLE55,@HOLE18,@HOLE22,@HOLE17,@HOLE48,@HOLE10,@HOLE43,@HOLE56,@HOLE13,@HOLE28,@HOLE2,@HOLE1,@HOLE70,@HOLE50,@HOLE60,@HOLE42,@HOLE9,@HOLE61,@HOLE65,@HOLE39,@HOLE36,@HOLE27,@HOLE32,@HOLE68,@HOLE20,@HOLE64,@HOLE66,@HOLE7,@HOLE29,@HOLE26,@HOLE52,@HOLE62,@HOLE58,@HOLE21,@HOLE49,@HOLE46,@HOLE5,@HOLE0,@HOLE8,@HOLE69,@HOLE30,@HOLE53,@HOLE63,@HOLE34";"";72;"";;;
2;"R1,R6,R3,R5,R2,R4";"0603";6;"1k";;;
3;"LOGO22,LOGO7,LOGO2,LOGO27,LOGO12,LOGO17,LOGO16,LOGO11,LOGO1,LOGO6,LOGO26,LOGO21";"QWIIC_5MM";12;"QWIIC_LOGO_5MM";;;
4;"J11,J1,J12,J4,J23,J15,J3,J10,J27,J16,J28,J19,J20,J6,J9,J18,J8,J17,J5,J29,J13,J22,J7,J30,J2,J25,J14,J26,J21,J24";"JST04_1MM_RA";30;"QWIIC_RIGHT_ANGLE";;;
5;"U$16,U$1,U$9,U$11,U$21,U$26";"PWR0";6;"";;;
6;"E$3,E$1,E$4,E$2";"FIDUCIAL-1X2";4;"";;;
7;"FD5,FD17,FD23,FD11,FD15,FD1,FD9,FD7,FD3,FD21,FD19,FD13,FD22,FD6,FD12,FD24,FD14,FD20,FD16,FD8,FD18,FD4,FD10,FD2";"FIDUCIAL-1X2";24;"FIDUCIAL1X2";;;
8;"U$18,U$23,U$3,U$13,U$7,U$28,U$24,U$8,U$5,U$14,U$29,U$19";"MULTISTAR0";12;"";;;
9;"D5,D1,D2,D3,D4,D6";"LED-0603";6;"RED";;;
10;"LOGO20,LOGO5,LOGO15,LOGO30,LOGO25,LOGO10,LOGO29,LOGO4,LOGO9,LOGO24,LOGO14,LOGO19";"SFE_LOGO_NAME_.2";12;"SFE_LOGO_NAME.2_INCH";;;
11;"U$17,U$12,U$2,U$27,U$22,U$4";"SFE_LOGO_FLAME_.2";6;"";;;
12;"E$5,E$6";"FIDUCIAL-1.5X3";2;"";;;
13;"U$15,U$20,U$25,U$30,U$10,U$6";"#PWR#0";6;"";;;
14;"LOGO8,LOGO13,LOGO23,LOGO18,LOGO3,LOGO28";"OSHW-LOGO-S";6;"OSHW-LOGOS";;;
15;"JP5,JP2,JP4,JP1,JP6,JP3";"SMT-JUMPER_2_NC_TRACE_SILK";6;"PWR_LED";;;

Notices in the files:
parts and their libraries:
Released under the Creative Commons Attribution Share-Alike 4.0 License
https://creativecommons.org/licenses/by-sa/4.0
